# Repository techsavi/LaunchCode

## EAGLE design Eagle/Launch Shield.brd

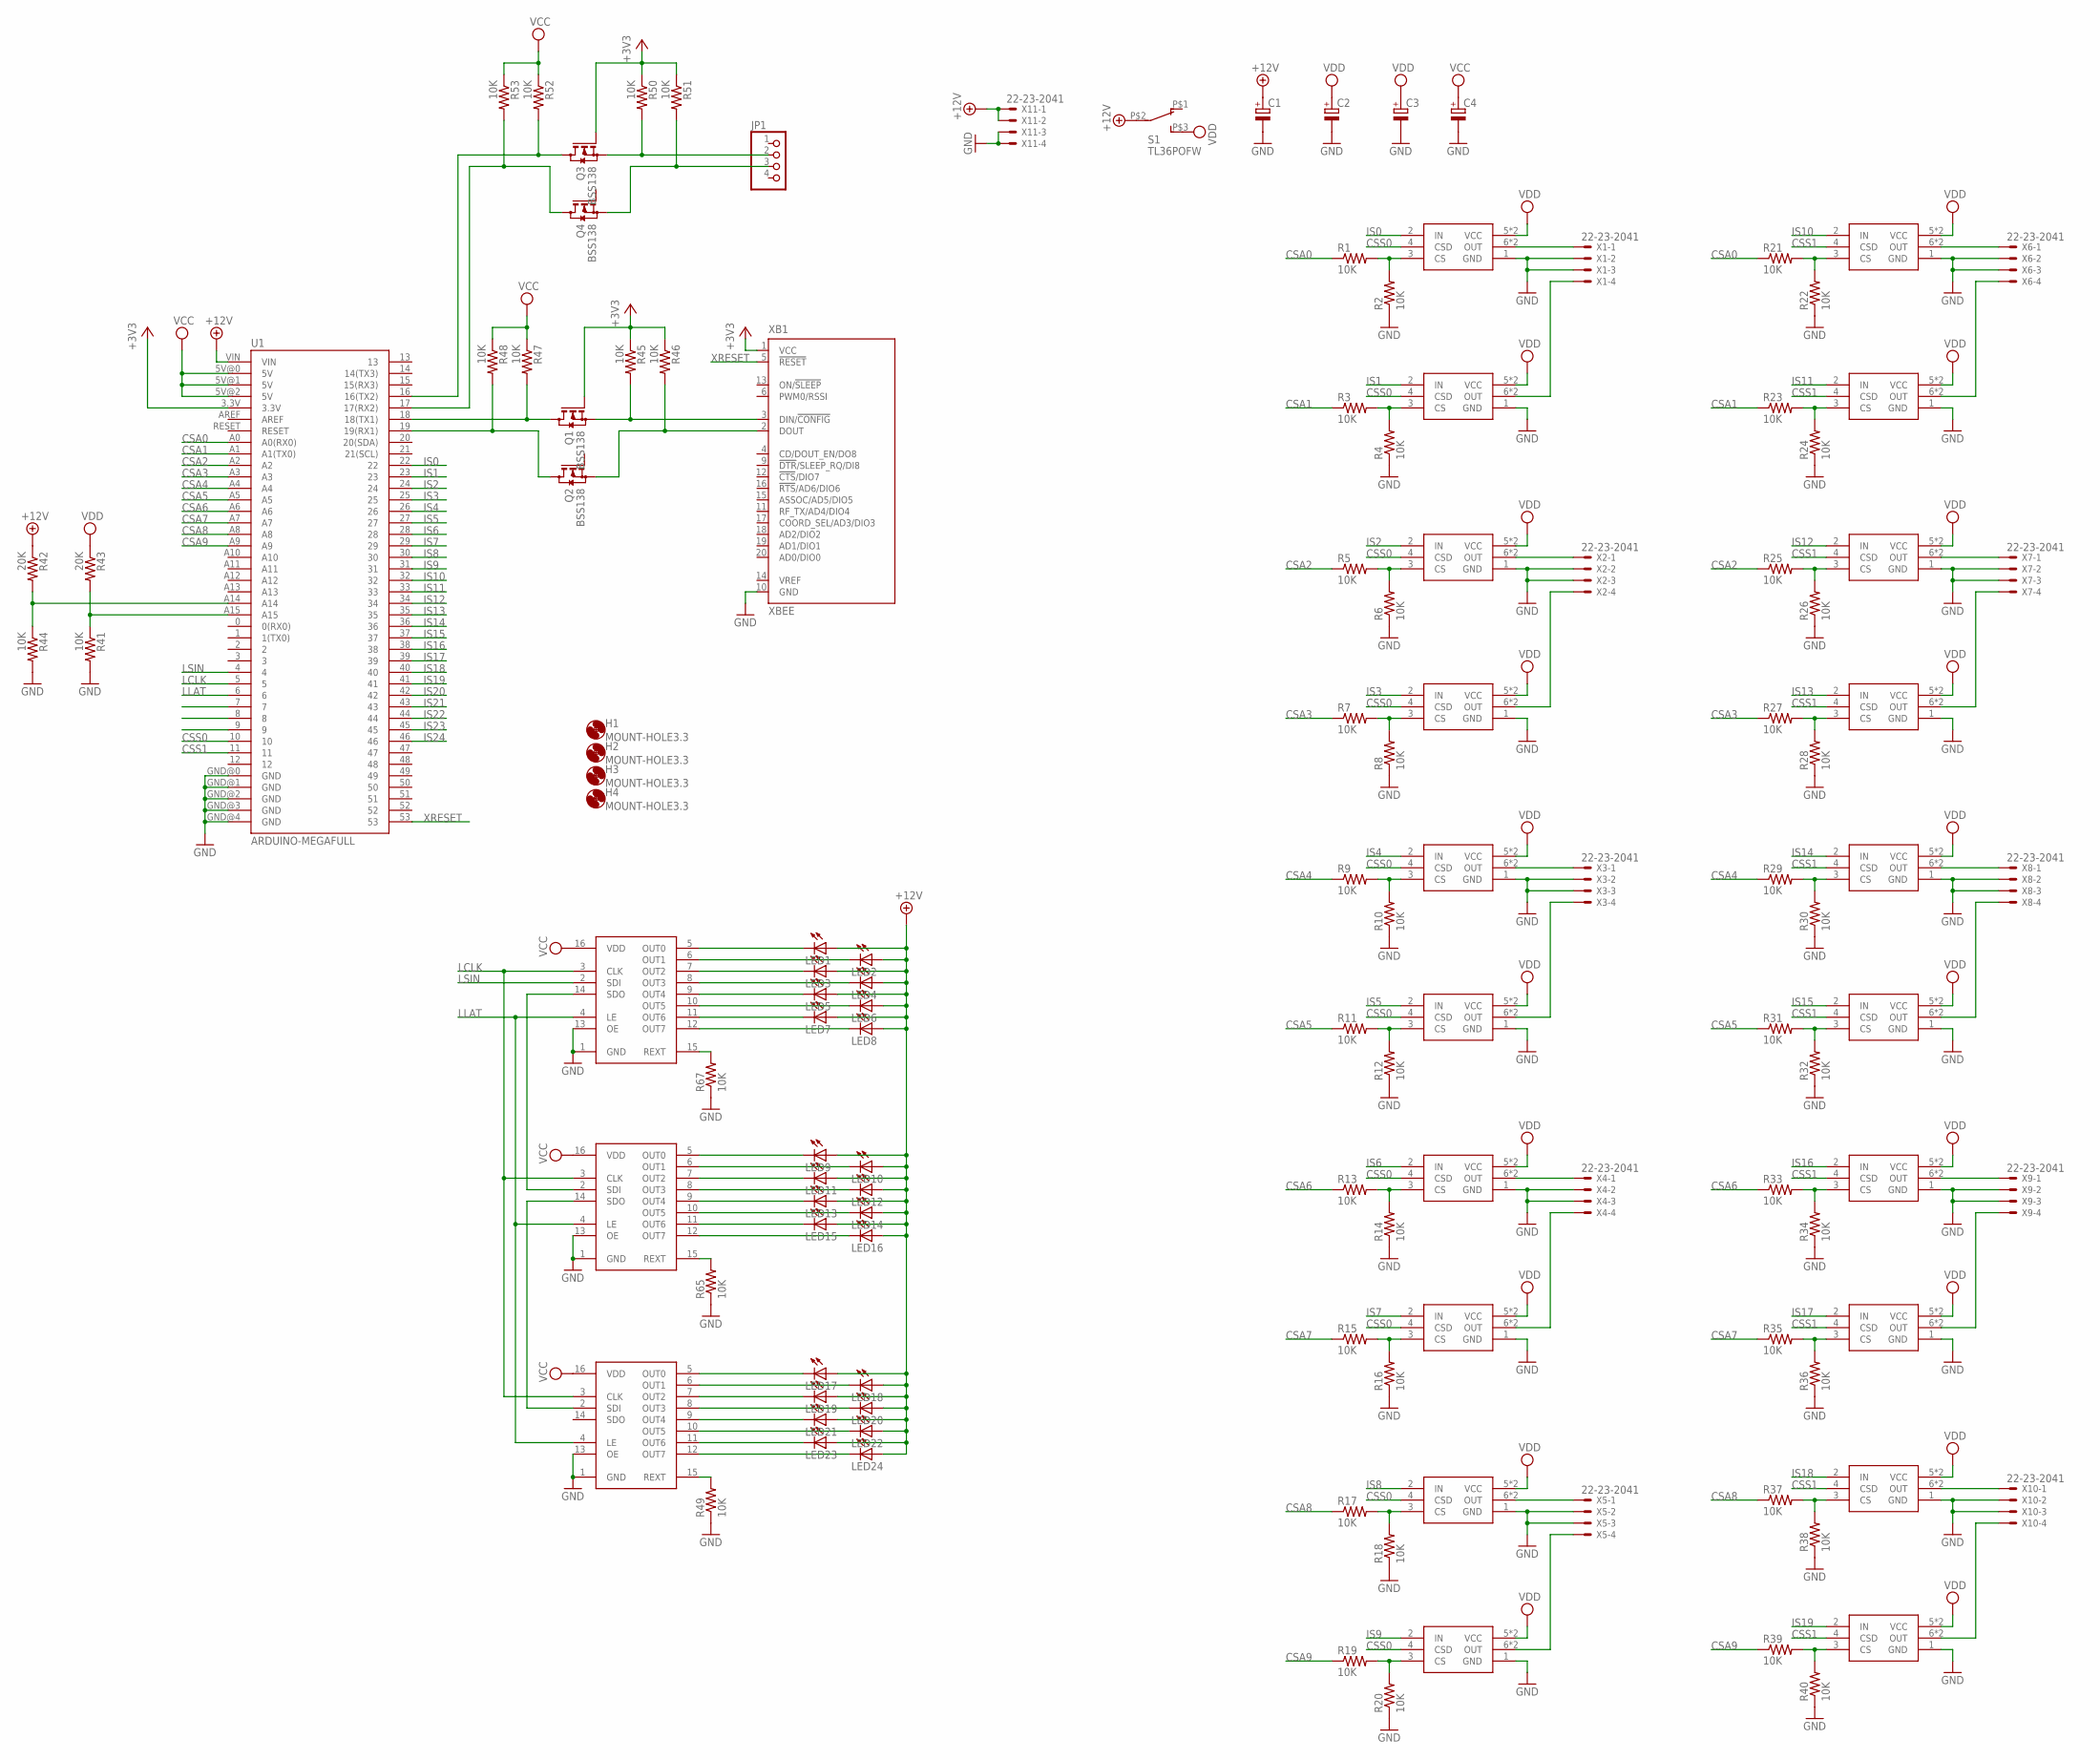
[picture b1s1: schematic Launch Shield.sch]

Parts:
C1, C2, C3, C4: CPOL-EUE5-6; E5-6
H1, H2, H3, H4: MOUNT-HOLE3.3; 3,3
JP1: PINHD-1X4; 1X04
LED1, LED2, LED3, LED4, LED5, LED6, LED7, LED8, LED9, LED10, LED11, LED12, LED13, LED14, LED15, LED16, LED17, LED18, LED19, LED20, LED21, LED22, LED23, LED24: LEDCHIPLED_0805; CHIPLED_0805
Q1, Q2, Q3, Q4: BSS138; SOT23
R1, R2, R3, R4, R5, R6, R7, R8, R9, R10, R11, R12, R13, R14, R15, R16, R17, R18, R19, R20, R21, R22, R23, R24, R25, R26, R27, R28, R29, R30, R31, R32, R33, R34, R35, R36, R37, R38, R39, R40, R41, R44, R45, R46, R47, R48, R49, R50, R51, R52, R53, R65, R67: 10K; R0603
R42, R43: 20K; R0603
S1: TL36POFW; TOGGLE
U1: ARDUINO-MEGAFULL; ARDUINO_MEGA
U$1, U$2, U$3, U$4, U$5, U$6, U$7, U$8, U$9, U$10, U$11, U$12, U$13, U$14, U$15, U$16, U$17, U$18, U$19, U$20: VN5E160MS-E; SOIC8
U$21, U$22, U$23: TLC5916; D_R-PDSO-G16
X1, X2, X3, X4, X5, X6, X7, X8, X9, X10, X11: 22-23-2041
XB1: XBEE

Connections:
+3V3: Q1.1 (G), Q3.1 (G), R45.1, R46.1, R50.1, R51.1, U1.3.3V, XB1.1 (VCC)
+12V: C1.+, LED1.A, LED2.A, LED3.A, LED4.A, LED5.A, LED6.A, LED7.A, LED8.A, LED9.A, LED10.A, LED11.A, LED12.A, LED13.A, LED14.A, LED15.A, LED16.A, LED17.A, LED18.A, LED19.A, LED20.A, LED21.A, LED22.A, LED23.A, LED24.A, R42.1, S1.P$2, U1.VIN, X11.1, X11.2
CSA0: R1.1, R21.1, U1.A0 (A0(RX0))
CSA1: R3.1, R23.1, U1.A1 (A1(TX0))
CSA2: R5.1, R25.1, U1.A2
CSA3: R7.1, R27.1, U1.A3
CSA4: R9.1, R29.1, U1.A4
CSA5: R11.1, R31.1, U1.A5
CSA6: R13.1, R33.1, U1.A6
CSA7: R15.1, R35.1, U1.A7
CSA8: R17.1, R37.1, U1.A8
CSA9: R19.1, R39.1, U1.A9
CSS0: U1.10, U$1.4 (CSD), U$2.4 (CSD), U$3.4 (CSD), U$4.4 (CSD), U$5.4 (CSD), U$6.4 (CSD), U$7.4 (CSD), U$8.4 (CSD), U$9.4 (CSD), U$10.4 (CSD)
CSS1: U1.11, U$11.4 (CSD), U$12.4 (CSD), U$13.4 (CSD), U$14.4 (CSD), U$15.4 (CSD), U$16.4 (CSD), U$17.4 (CSD), U$18.4 (CSD), U$19.4 (CSD), U$20.4 (CSD)
GND: C1.-, C2.-, C3.-, C4.-, R2.1, R4.1, R6.1, R8.1, R10.1, R12.1, R14.1, R16.1, R18.1, R20.1, R22.1, R24.1, R26.1, R28.1, R30.1, R32.1, R34.1, R36.1, R38.1, R40.1, R41.2, R44.2, R49.1, R65.1, R67.1, U1.GND@0 (GND), U1.GND@1 (GND), U1.GND@2 (GND), U1.GND@3 (GND), U1.GND@4 (GND), U$1.1 (GND), U$2.1 (GND), U$3.1 (GND), U$4.1 (GND), U$5.1 (GND), U$6.1 (GND), U$7.1 (GND), U$8.1 (GND), U$9.1 (GND), U$10.1 (GND), U$11.1 (GND), U$12.1 (GND), U$13.1 (GND), U$14.1 (GND), U$15.1 (GND), U$16.1 (GND), U$17.1 (GND), U$18.1 (GND), U$19.1 (GND), U$20.1 (GND), U$21.1 (GND), U$21.13 (OE), U$22.1 (GND), U$22.13 (OE), U$23.1 (GND), U$23.13 (OE), X1.2, X1.3, X2.2, X2.3, X3.2, X3.3, X4.2, X4.3, X5.2, X5.3, X6.2, X6.3, X7.2, X7.3, X8.2, X8.3, X9.2, X9.3, X10.2, X10.3, X11.3, X11.4, XB1.10 (GND)
IS0: U1.22, U$1.2 (IN)
IS1: U1.23, U$2.2 (IN)
IS2: U1.24, U$3.2 (IN)
IS3: U1.25, U$4.2 (IN)
IS4: U1.26, U$5.2 (IN)
IS5: U1.27, U$6.2 (IN)
IS6: U1.28, U$7.2 (IN)
IS7: U1.29, U$8.2 (IN)
IS8: U1.30, U$9.2 (IN)
IS9: U1.31, U$10.2 (IN)
IS10: U1.32, U$11.2 (IN)
IS11: U1.33, U$12.2 (IN)
IS12: U1.34, U$13.2 (IN)
IS13: U1.35, U$14.2 (IN)
IS14: U1.36, U$15.2 (IN)
IS15: U1.37, U$16.2 (IN)
IS16: U1.38, U$17.2 (IN)
IS17: U1.39, U$18.2 (IN)
IS18: U1.40, U$19.2 (IN)
IS19: U1.41, U$20.2 (IN)
IS20: U1.42
IS21: U1.43
IS22: U1.44
IS23: U1.45
IS24: U1.46
LCLK: U1.5, U$21.3 (CLK), U$22.3 (CLK), U$23.3 (CLK)
LLAT: U1.6, U$21.4 (LE), U$22.4 (LE), U$23.4 (LE)
LSIN: U1.4, U$21.2 (SDI)
unnamed: U$1.6 (OUT), U$1.7 (OUT), X1.1
unnamed: R1.2, R2.2, U$1.3 (CS)
unnamed: R3.2, R4.2, U$2.3 (CS)
unnamed: U$2.6 (OUT), U$2.7 (OUT), X1.4
unnamed: R5.2, R6.2, U$3.3 (CS)
unnamed: U$10.6 (OUT), U$10.7 (OUT), X5.4
unnamed: R7.2, R8.2, U$4.3 (CS)
unnamed: U$4.6 (OUT), U$4.7 (OUT), X2.4
unnamed: R9.2, R10.2, U$5.3 (CS)
unnamed: U$5.6 (OUT), U$5.7 (OUT), X3.1
unnamed: R11.2, R12.2, U$6.3 (CS)
unnamed: U$11.6 (OUT), U$11.7 (OUT), X6.1
unnamed: R13.2, R14.2, U$7.3 (CS)
unnamed: U$12.6 (OUT), U$12.7 (OUT), X6.4
unnamed: R15.2, R16.2, U$8.3 (CS)
unnamed: U$18.6 (OUT), U$18.7 (OUT), X9.4
unnamed: R17.2, R18.2, U$9.3 (CS)
unnamed: R42.2, R44.1, U1.A14
unnamed: R19.2, R20.2, U$10.3 (CS)
unnamed: R41.1, R43.2, U1.A15
unnamed: R21.2, R22.2, U$11.3 (CS)
unnamed: Q2.2 (S), R46.2, XB1.2 (DOUT)
unnamed: R23.2, R24.2, U$12.3 (CS)
unnamed: Q1.2 (S), R45.2, XB1.3 (DIN/!CONFIG)
unnamed: R25.2, R26.2, U$13.3 (CS)
unnamed: U$13.6 (OUT), U$13.7 (OUT), X7.1
unnamed: R27.2, R28.2, U$14.3 (CS)
unnamed: R49.2, U$23.15 (REXT)
unnamed: R29.2, R30.2, U$15.3 (CS)
unnamed: U$15.6 (OUT), U$15.7 (OUT), X8.1
unnamed: R31.2, R32.2, U$16.3 (CS)
unnamed: U$14.6 (OUT), U$14.7 (OUT), X7.4
unnamed: R33.2, R34.2, U$17.3 (CS)
unnamed: U$17.6 (OUT), U$17.7 (OUT), X9.1
unnamed: R35.2, R36.2, U$18.3 (CS)
unnamed: Q1.3 (D), R47.2, U1.18 (18(TX1))
unnamed: R37.2, R38.2, U$19.3 (CS)
unnamed: U$19.6 (OUT), U$19.7 (OUT), X10.1
unnamed: R39.2, R40.2, U$20.3 (CS)
unnamed: U$16.6 (OUT), U$16.7 (OUT), X8.4
unnamed: Q2.3 (D), R48.2, U1.19 (19(RX1))
unnamed: R65.2, U$22.15 (REXT)
unnamed: R67.2, U$21.15 (REXT)
unnamed: U$3.6 (OUT), U$3.7 (OUT), X2.1
unnamed: U$21.14 (SDO), U$22.2 (SDI)
unnamed: U$22.14 (SDO), U$23.2 (SDI)
unnamed: LED8.C, U$21.12 (OUT7)
unnamed: LED7.C, U$21.11 (OUT6)
unnamed: U$6.6 (OUT), U$6.7 (OUT), X3.4
unnamed: LED6.C, U$21.10 (OUT5)
unnamed: U$20.6 (OUT), U$20.7 (OUT), X10.4
unnamed: U$7.6 (OUT), U$7.7 (OUT), X4.1
unnamed: U$8.6 (OUT), U$8.7 (OUT), X4.4
unnamed: U$9.6 (OUT), U$9.7 (OUT), X5.1
unnamed: LED5.C, U$21.9 (OUT4)
unnamed: LED4.C, U$21.8 (OUT3)
unnamed: LED3.C, U$21.7 (OUT2)
unnamed: LED2.C, U$21.6 (OUT1)
unnamed: LED1.C, U$21.5 (OUT0)
unnamed: LED9.C, U$22.5 (OUT0)
unnamed: LED10.C, U$22.6 (OUT1)
unnamed: LED11.C, U$22.7 (OUT2)
unnamed: LED12.C, U$22.8 (OUT3)
unnamed: LED13.C, U$22.9 (OUT4)
unnamed: LED14.C, U$22.10 (OUT5)
unnamed: LED15.C, U$22.11 (OUT6)
unnamed: LED16.C, U$22.12 (OUT7)
unnamed: LED17.C, U$23.5 (OUT0)
unnamed: LED18.C, U$23.6 (OUT1)
unnamed: LED19.C, U$23.7 (OUT2)
unnamed: LED20.C, U$23.8 (OUT3)
unnamed: LED21.C, U$23.9 (OUT4)
unnamed: LED22.C, U$23.10 (OUT5)
unnamed: LED23.C, U$23.11 (OUT6)
unnamed: LED24.C, U$23.12 (OUT7)
unnamed: JP1.3, Q4.2 (S), R51.2
unnamed: JP1.2, Q3.2 (S), R50.2
unnamed: Q3.3 (D), R52.2, U1.16 (16(TX2))
unnamed: Q4.3 (D), R53.2, U1.17 (17(RX2))
VCC: C4.+, R47.1, R48.1, R52.1, R53.1, U1.5V@0 (5V), U1.5V@1 (5V), U1.5V@2 (5V), U$21.16 (VDD), U$22.16 (VDD), U$23.16 (VDD)
VDD: C2.+, C3.+, R43.1, S1.P$3 (S), U$1.5 (VCC), U$1.8 (VCC), U$2.5 (VCC), U$2.8 (VCC), U$3.5 (VCC), U$3.8 (VCC), U$4.5 (VCC), U$4.8 (VCC), U$5.5 (VCC), U$5.8 (VCC), U$6.5 (VCC), U$6.8 (VCC), U$7.5 (VCC), U$7.8 (VCC), U$8.5 (VCC), U$8.8 (VCC), U$9.5 (VCC), U$9.8 (VCC), U$10.5 (VCC), U$10.8 (VCC), U$11.5 (VCC), U$11.8 (VCC), U$12.5 (VCC), U$12.8 (VCC), U$13.5 (VCC), U$13.8 (VCC), U$14.5 (VCC), U$14.8 (VCC), U$15.5 (VCC), U$15.8 (VCC), U$16.5 (VCC), U$16.8 (VCC), U$17.5 (VCC), U$17.8 (VCC), U$18.5 (VCC), U$18.8 (VCC), U$19.5 (VCC), U$19.8 (VCC), U$20.5 (VCC), U$20.8 (VCC)
XRESET: U1.53, XB1.5 (!RESET)

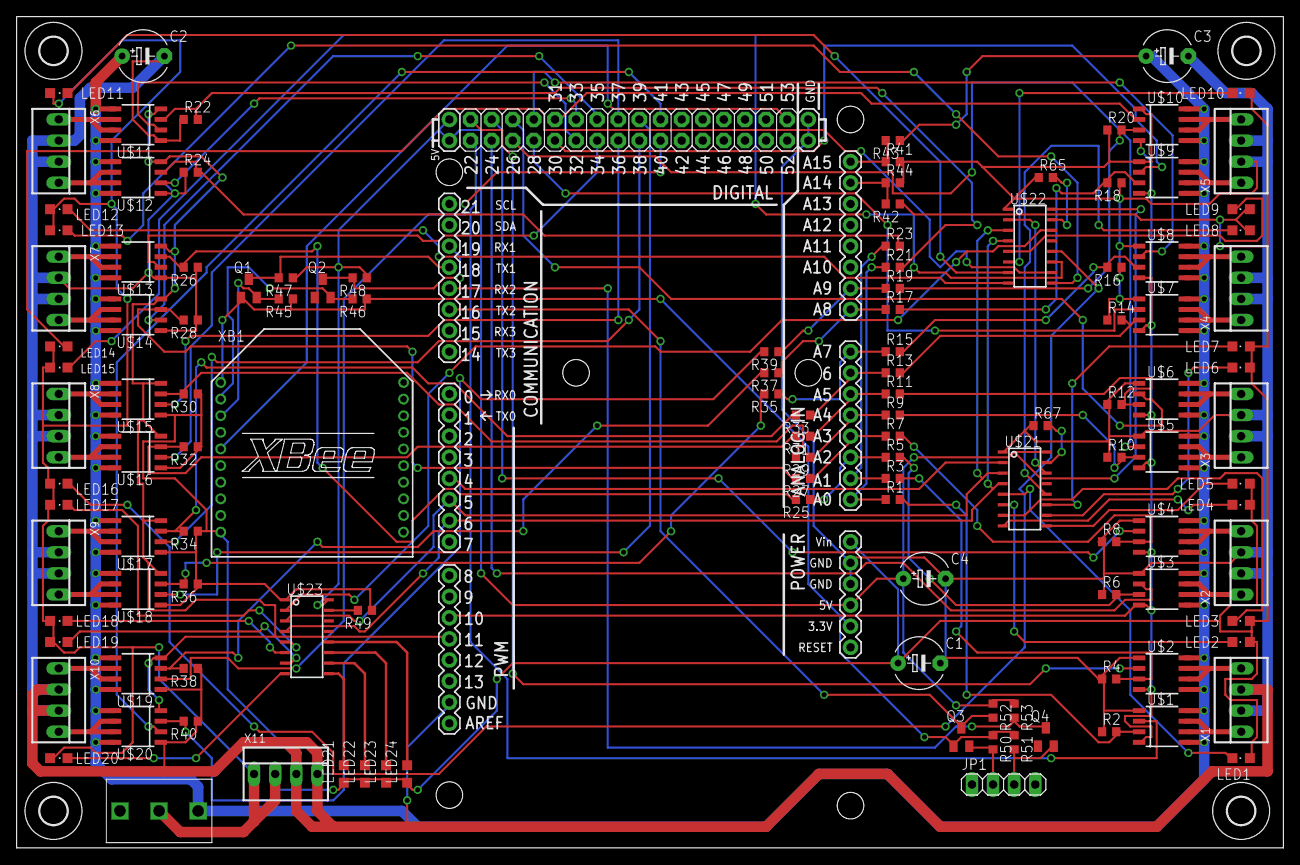
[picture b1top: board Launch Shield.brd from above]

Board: 2 copper layers, 152.4 x 100.0 mm, 129 parts (0 on the bottom side), 120 nets.

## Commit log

2015-06-19 2014 version
2015-06-19 Move to Pi folder
2015-06-19 Arduino control code
2015-06-25 Add Eagle files

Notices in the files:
parts and their libraries:
SparkFun-Boards: Licensing: Creative Commons ShareAlike 4.0 International - https://creativecommons.org/licenses/by-sa/4.0
